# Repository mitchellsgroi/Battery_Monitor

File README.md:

# Battery_Monitor

Use to monitor Voltage, Current and Amp-Hours of a single 12V sealed lead acid battery.
Also includes temperature monitoring for a fridge freezer.

## About

Despite what 4x4 and caravan accessory companies seem to advertise the state of charge (SoC) of lead acid batteries cannot be determined by measuring voltage alone.

I have created this little Arduino based device to measure the amp-hours that have flowed in and out of the battery to give a more accurate representation of the SoC and hopefully help keep the battery from being overly discharged.

A fairly unique feature of this project is that there is no usage of a shunt to measure current. This is instead achieved by a current sensing coil via hall effect. Therefore installation of the device requires very little modification to existing battery systems.

There is also a demo website included in this repo that gives a basic representation of the monitor in use.

## Notes

- Currently in the process of cleaning everything up after not having being
  touched in over 3 years.

- There are 3 working prototypes in existence that have been running without
  incident now for about 4 or more years including 1 with the current sensor
  mounted in the engine bay.

- I am not going to provide any usage instructions or license at this stage
  until I sort everything out and package it up properly. 

- Contact me if you have any interest in this project and I will help out where I can.

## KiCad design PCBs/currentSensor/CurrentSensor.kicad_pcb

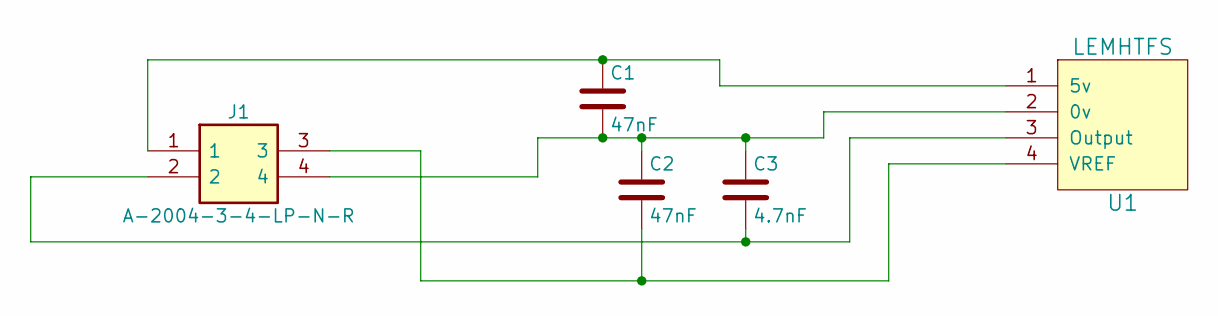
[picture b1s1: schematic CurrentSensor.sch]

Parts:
C1, C2: 47nF; C_Disc_D4.7mm_W2.5mm_P5.00mm
C3: 4.7nF; C_Disc_D5.0mm_W2.5mm_P2.50mm
J1: A-2004-3-4-LP-N-R; Manufacturer_Part_Number A-2004-3-4-LP-N-R
U1: LEMHTFS; HTFS-Series_LEM-HallEffektCurrentTransducer

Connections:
unnamed: C1.1, J1.1, U1.1 (5v)
unnamed: C1.2, C2.1, C3.1, J1.4, U1.2 (0v)
unnamed: C2.2, J1.3, U1.4 (VREF)
unnamed: C3.2, J1.2, U1.3 (Output)

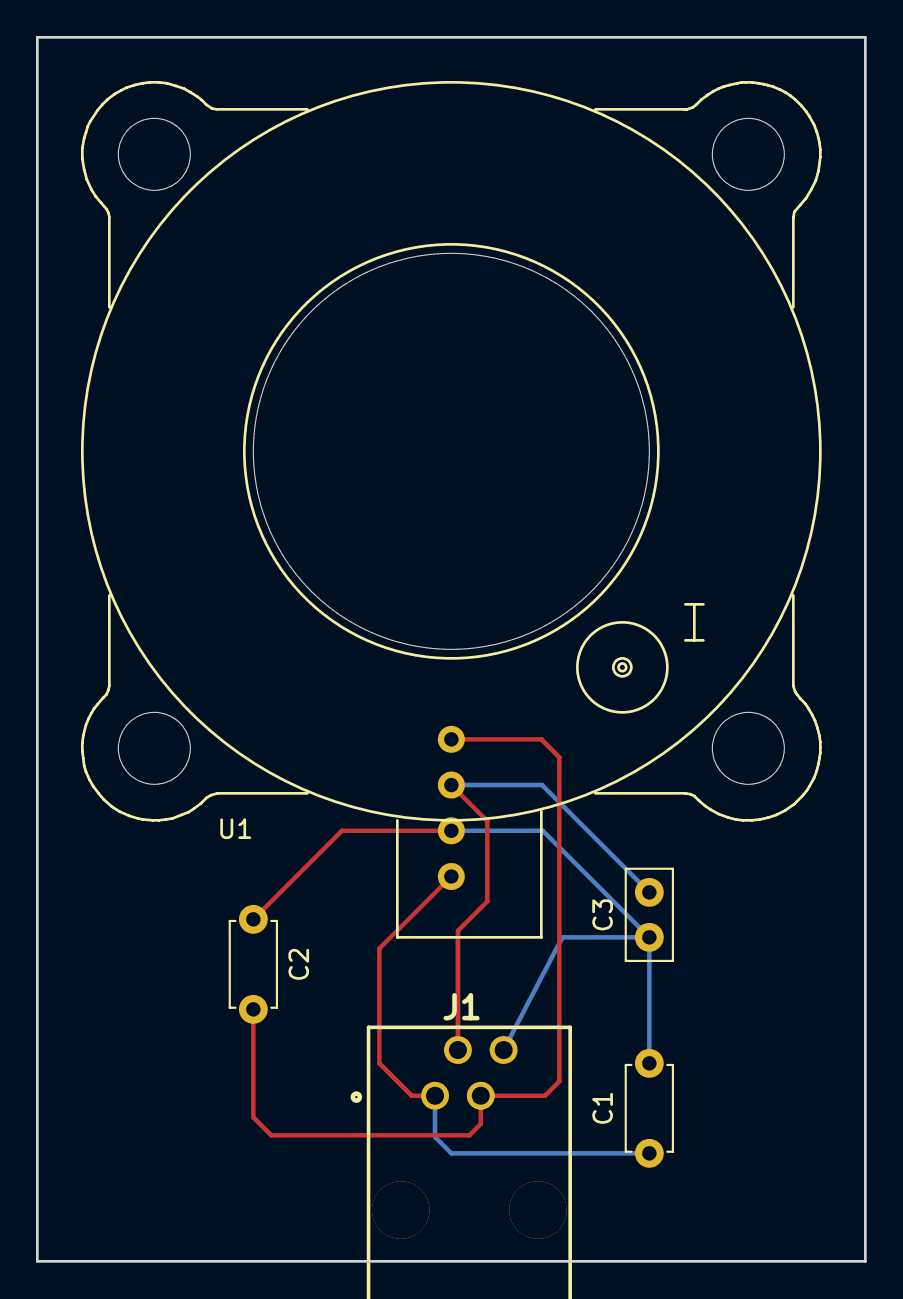
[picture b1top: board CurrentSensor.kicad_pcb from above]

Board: 2 copper layers, 46.0 x 68.0 mm, 5 parts (0 on the bottom side), 4 nets.

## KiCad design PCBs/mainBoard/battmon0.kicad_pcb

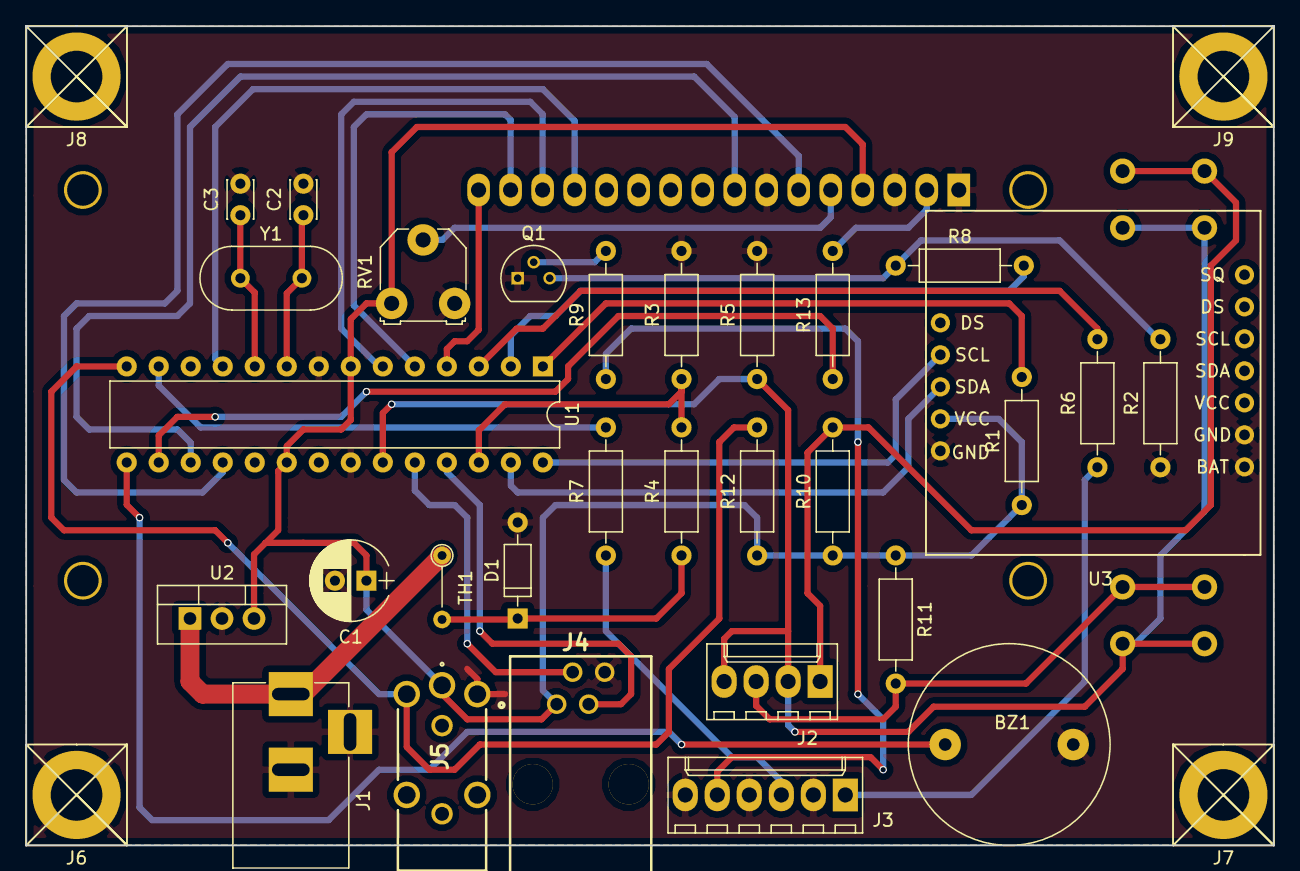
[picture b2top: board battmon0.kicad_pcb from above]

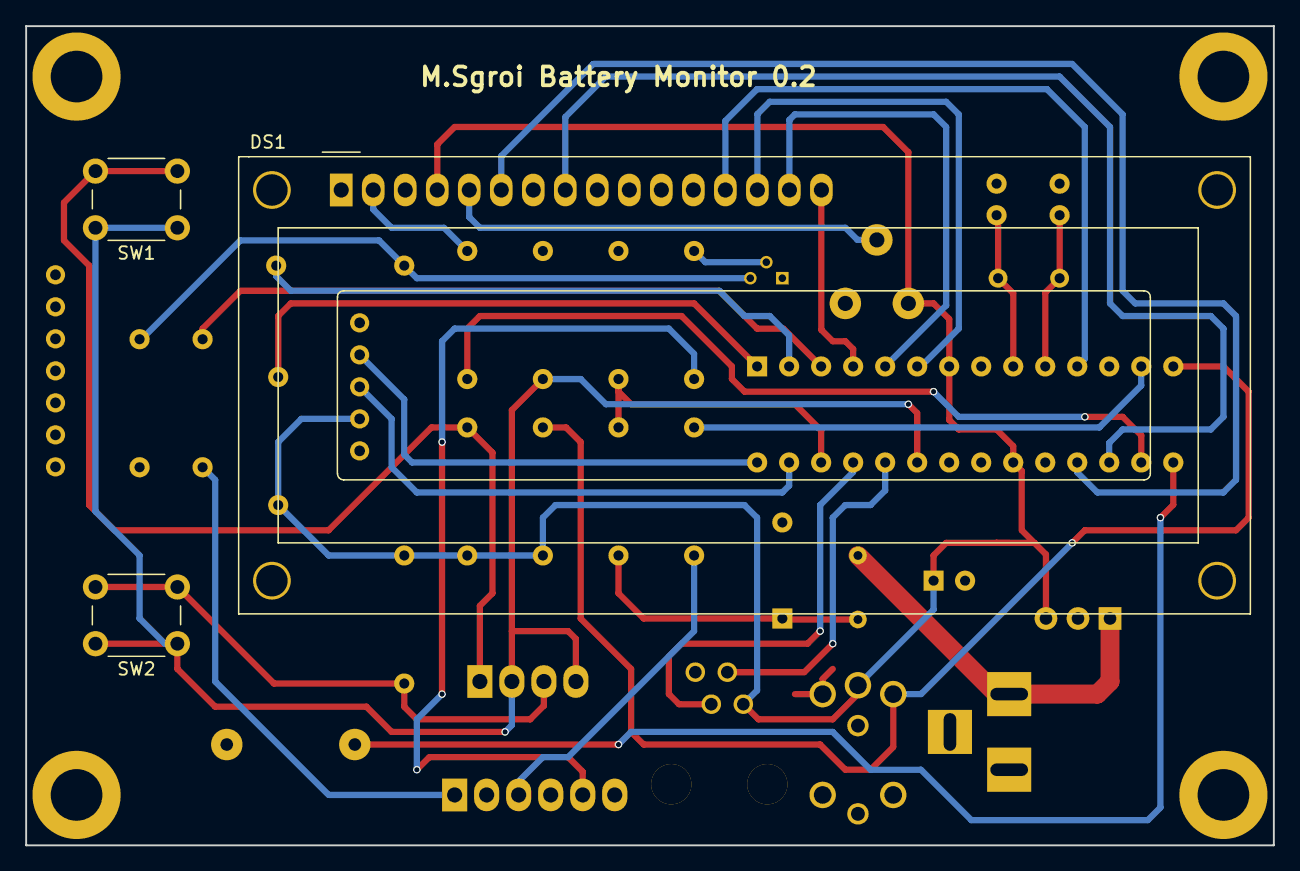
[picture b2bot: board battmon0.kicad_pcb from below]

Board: 2 copper layers, 99.0 x 65.0 mm, 37 parts (3 on the bottom side), 34 nets.

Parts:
BZ1: Buzzer; BUZZER
C1: 100uf; CP_Radial_D6.3mm_P2.50mm
C2, C3: 22pf; C_Disc_D3.0mm_W2.0mm_P2.50mm
D1: D_Zener; D_DO-35_SOD27_P7.62mm_Horizontal
DS1: HY1602E; WC1602A
J1: Barrel_Jack; BARREL_JACK
J2: BUTTONS; Molex_KK-6410-04_04x2.54mm_Straight
J3: I/O; Molex_KK-6410-06_06x2.54mm_Straight
J4: A-2004-3-4-LP-N-R
J5: 1503_19; 1503-19
J6, J7, J8, J9: Conn_01x01; Mounthole
Q1: 2N3904; TO-92_Molded_Narrow
R1: 10K; R_Axial_DIN0207_L6.3mm_D2.5mm_P10.16mm_Horizontal
R2, R6, R7, R8, R9, R13: 220R; R_Axial_DIN0207_L6.3mm_D2.5mm_P10.16mm_Horizontal
R3: 4M7; R_Axial_DIN0207_L6.3mm_D2.5mm_P10.16mm_Horizontal
R4: 10M; R_Axial_DIN0207_L6.3mm_D2.5mm_P10.16mm_Horizontal
R5, R10: 10k; R_Axial_DIN0207_L6.3mm_D2.5mm_P10.16mm_Horizontal
R11: 100k; R_Axial_DIN0207_L6.3mm_D2.5mm_P10.16mm_Horizontal
R12: 4k7; R_Axial_DIN0207_L6.3mm_D2.5mm_P10.16mm_Horizontal
RV1: POT; Potentiometer_Triwood_RM-065
SW1, SW2: SW_Push; SW_PUSH_6mm_h9.5mm
TH1: Thermistor_PTC; R_Axial_DIN0204_L3.6mm_D1.6mm_P5.08mm_Vertical
U1: ATMEGA328-PU; DIP-28_W7.62mm
U2: LM7805_TO220; TO-220-3_Vertical
U3: TinyRTC
Y1: 16Mhz; Crystal_HC49-U_Vertical

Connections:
+5V: C1.1, DS1.4, J4.1, J5.1, R1.1, R10.1, R11.1, R12.1, RV1.1, U1.7, U1.20, U2.3, U3.2
+12V: J1.1, TH1.1, U2.1
/ANALOG0: J2.2, J2.4, R5.1, SW1.1, SW2.1, U1.23
/ANALOG1: J4.2, U1.24
/ANALOG2: J4.3, U1.25
/ANALOG3: R3.1, R4.2, U1.26
/ANALOG4: U1.27, U3.3
/ANALOG5: U1.28, U3.4
/CLOCK1: C2.1, U1.9, Y1.2
/CLOCK2: C3.1, U1.10, Y1.1
/DIGITAL0: R8.2, U1.2
/DIGITAL1: R6.2, U1.3
/DIGITAL2: DS1.16, U1.4
/DIGITAL3: DS1.15, U1.5
/DIGITAL4: DS1.14, U1.6
/DIGITAL5: DS1.13, U1.11
/DIGITAL7: R7.2, U1.13
/DIGITAL8: J5.2, R12.2, U1.14
/DIGITAL9: BZ1.1, U1.15
/DIGITAL10: R13.1, U1.16
/DIGITAL11: DS1.8, U1.17
/DIGITAL12: DS1.6, U1.18
/RESET: R1.2, U1.1
GND: BZ1.2, C1.2, C2.2, C3.2, D1.2, DS1.1, DS1.3, DS1.7, J1.2, J1.3, J3.2, J3.4, J3.6, J4.4, J5.3, J6.1, Q1.1, R2.1, R3.2, R5.2, RV1.3, U1.8, U1.22, U2.2, U3.1, U3.6, U3.7
unnamed: D1.1, R4.1, TH1.2
unnamed: DS1.2, R13.2
unnamed: DS1.5, RV1.2
unnamed: J2.1, R10.2, SW1.2
unnamed: J2.3, R11.2, SW2.2
unnamed: J3.1, R6.1
unnamed: J3.3, R7.1
unnamed: J3.5, R9.1
unnamed: Q1.2, R9.2
unnamed: Q1.3, R2.2, R8.1

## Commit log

2018-03-24 Further setup of repo
    Added TODOs and BUGS to readme.
    Fixed folder structure to suit arduino ide
2018-05-13 add RTC test
    Added a sketch for testing the RTC.
    Adds 1 every second and prints the number to the LCD. Use stopwatch to compare accuracy.
2018-05-13 add second counter for comparison
    Second counter using the chip clock to count up. Compare for to check accuracy.
2018-05-14 Make buttons work
    Delete all old code and start from scratch. Make the buttons count when pressed
2018-05-14 add screen placeholders
    Adjusted buttons, added screen placeholders, implemented RTC second counting
2018-05-15 add volt reading and smoothing, add amphour symbol
2018-05-16 Set up alarm screens
    Made the alarm screens work. added amp hour reset functionality. Added return to home screen automatically
2018-05-17 Fix access to setup menu
    Can now enter and exit the settings menu
2018-05-18 add TODO, Change Variables
2018-05-18 Furthur develop setup screens
2018-05-19 Develop setting screens
    Addes flash function to create faux cursor. Solved some issues with the RTC.
2018-05-19 Nut out pointer stuff for buttons
2018-05-19 develop settings screens
    Make the temperature alarm setting screens work
2018-05-20 Start work on EEPROM read/write
2018-05-20 Adjust EEPROM R/W
2018-05-21 Function Everything
    Move all code out of loop and into functions. Start work on the alarms
2018-05-21 Volt and Temp alarms
    Made the alarms trigger at the set values
2018-05-22 Write and test alarm functions
2018-05-23 Make thermometer and current reading work
2018-05-23 add psudocode for testing function
2018-05-23 Capacity Tester
2018-05-26 work towards full PCB compatibility
2018-05-27 add softwire
2018-05-27 scrap softwire
2018-05-27 Revert "work towards full PCB compatibility"
    This reverts commit 5e2b64584d89cdf549f13917bd7779cb2c238dab.
2018-05-27 mess up reverting
2018-05-27 Revert "scrap softwire"
    This reverts commit 2c057f420a9aba92f44af993ab14fa2e42b0b61f.
2018-05-28 add timer to float detect
2018-05-31 Stabilise Current Readings
    Current readings were erratic during testing. Added a layer of smoothing to each analog pin before combining and smoothing again.
2018-05-31 Comment and fix backlight bug
2018-06-01 Adjust volt alarm screen
2018-06-01 Add multi temp probe testing
2018-06-13 work through support for mulitple temp probes
2018-06-14 Make fully functional with two temp probes
    Ready for field testing
2018-06-16 Refactor volt limit setup screen
    New function similar to the temperature setup
2018-09-09 Fix settings test to work with one temp probe
2018-09-13 add kvolts to PROTO variables
2018-12-04 Prepare test vehicle Installation
    Stephens Landcruiser
2021-08-02 Remove uneeded files/dirs
2021-08-02 Clean up file
2021-08-02 Add Kicad PCB Projects
2021-08-02 Cleanup Directories
2021-08-03 Add demo webpage
